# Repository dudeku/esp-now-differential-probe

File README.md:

# ESP-NOW Differential Probe Project

K. Dudek

### Framework: arduino-espressif32
>ver: 2.0.17
#### Lib Fixes:

```
in Ethernet.h
    class EthernetServer : public Server
    ->
    class EthernetServer : public Print
```

OR
```
in Ethernet.h in line 261:
	virtual void begin();
    ->
	virtual void begin(uint16_t port=0);

and in EthernetServer.cpp in line 28:
    void EthernetServer::begin()
    ->
    void EthernetServer::begin(uint16_t port_not_used)
```

#### Problems in framework version 3.x:
```
spi3 problem, not setting pinMode MISO (6)
[ ][E][esp32-hal-gpio.c:190] __digitalRead(): IO 6 is not set as GPIO.
```
### tool-esptoolpy @ 4.8.1

## Possible fix for framework 3.x
```
digitalRead() in LTC2449 lib cannot access MISO pin to check if transmission has been completed.

need to change LIC2449 library implementation for new version.
```

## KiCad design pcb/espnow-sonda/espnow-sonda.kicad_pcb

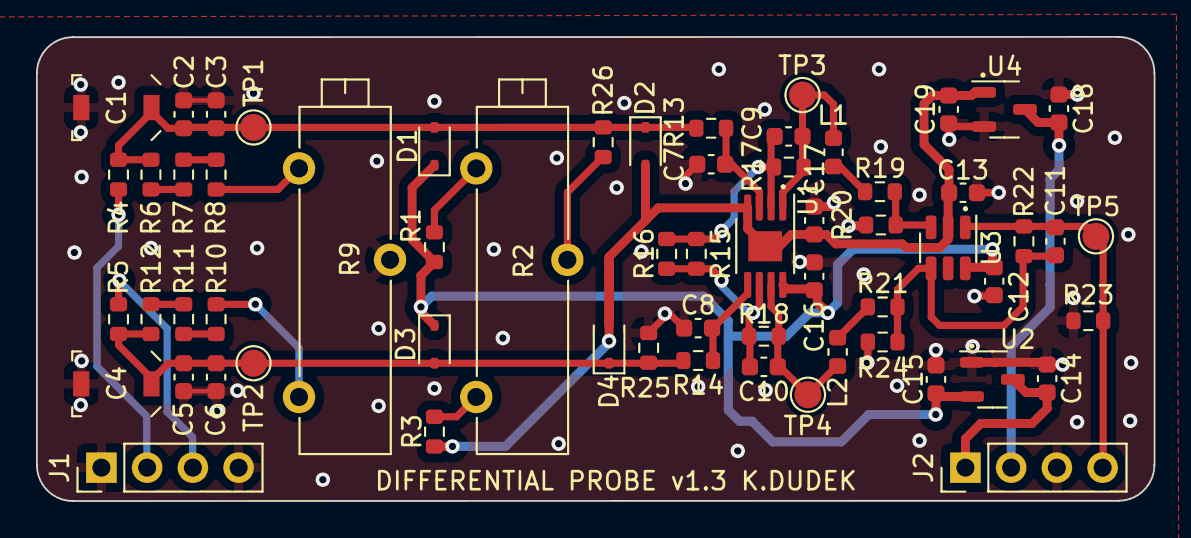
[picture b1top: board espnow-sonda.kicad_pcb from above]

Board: 2 copper layers, 62.1 x 25.8 mm, 62 parts (0 on the bottom side), 29 nets.

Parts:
C1, C4: C_Trimmer_Voltronics_JZ
C2, C3, C5, C6: C_0603_1608Metric
C7, C8, C9, C10, C11: 10p; C_0603_1608Metric
C12, C13, C16, C17: 0.1µ; C_0603_1608Metric
C14, C15, C18, C19: 1µ; C_0603_1608Metric
D1, D2, D3, D4: BAS316,115; D_SOD-323
J1, J2: PinHeader_1x04_P2.54mm_Vertical
L1, L2: r0; L_0603_1608Metric
R1, R3: 1M; R_0603_1608Metric
R2: 1M; Potentiometer_Bourns_3006W_Horizontal
R4, R5, R13, R14: 150; R_0603_1608Metric
R6, R12: 9.1k; R_0603_1608Metric
R7, R11: 845; R_0603_1608Metric
R8, R10: 24.9; R_0603_1608Metric
R9: 100; Potentiometer_Bourns_3006W_Horizontal
R15: 16; R_0603_1608Metric
R16, R24: R_0603_1608Metric
R17, R18: 470; R_0603_1608Metric
R19, R20, R21, R22: 348; R_0603_1608Metric
R23: 1k; R_0603_1608Metric
R25, R26: 750k; R_0603_1608Metric
TP1, TP2, TP4, TP5: TestPoint_Pad_D1.5mm
TP3: Test Point; TestPoint_Pad_D1.5mm
U1: LTC6269; MSOP-8-1EP_3x3mm_P0.65mm_EP1.68x1.88mm
U2: XC6206P251; SOT-23-3
U3: LMH6611; SOT-23-6
U4: XC6902N251; SOT-23-3

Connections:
4V8: C12.2, C15.2, C16.2, D1.1, D3.1, R1.1, U1.8 (V+), U2.2 (VO), U3.6 (V+)
-4V8: C13.2, C17.2, C19.2, D2.2, D4.2, R3.2, U1.4 (V-), U1.9 (V-), U3.2 (V-), U4.1 (VO)
/IN_N: J1.3, R5.1
/IN_P: J1.2, R4.1
/VCC5V: C14.2, J2.1, U2.3 (VI)
/VEE-5V: C18.2, J2.2, U4.3 (VI)
/VOUT: C11.2, J2.4, R22.2, R23.2, TP5.1 (TP), U3.1
GND: C1.2, C2.1, C3.1, C4.2, C5.1, C6.1, C7.1, C8.1, C12.1, C13.1, C14.1, C15.1, C16.1, C17.1, C18.1, C19.1, J1.1, J1.4, J2.3, R9.2, R20.2, R23.1, R24.1, R25.1, U2.1 (GND), U4.2 (GND)
unnamed: L1.2, R19.1
unnamed: L2.2, R21.1
unnamed: R1.2, R2.3
unnamed: R2.1, R3.1
unnamed: R2.2, R26.1
unnamed: R6.1, R7.2
unnamed: R7.1, R8.2
unnamed: R8.1, R9.3
unnamed: R9.1, R10.1
unnamed: R10.2, R11.1
unnamed: R11.2, R12.1
unnamed: C1.1, C2.2, C3.2, D1.2, D2.1, R4.2, R6.2, R13.1, R26.2, TP1.1 (TP)
unnamed: C4.1, C5.2, C6.2, D3.2, D4.1, R5.2, R12.2, R14.1, R25.2, TP2.1 (TP)
unnamed: C9.2, L1.1, R17.2, TP3.1 (TP), U1.1
unnamed: C10.2, L2.1, R18.2, TP4.1 (TP), U1.7
unnamed: C7.2, R13.2, U1.3 (+)
unnamed: C9.1, R15.1, R16.1, R17.1, U1.2 (-)
unnamed: C8.2, R14.2, U1.5 (+)
unnamed: C10.1, R15.2, R16.2, R18.1, U1.6 (-)
unnamed: R19.2, R20.1, U3.3 (+)
unnamed: C11.1, R21.2, R22.1, R24.2, U3.4 (-)

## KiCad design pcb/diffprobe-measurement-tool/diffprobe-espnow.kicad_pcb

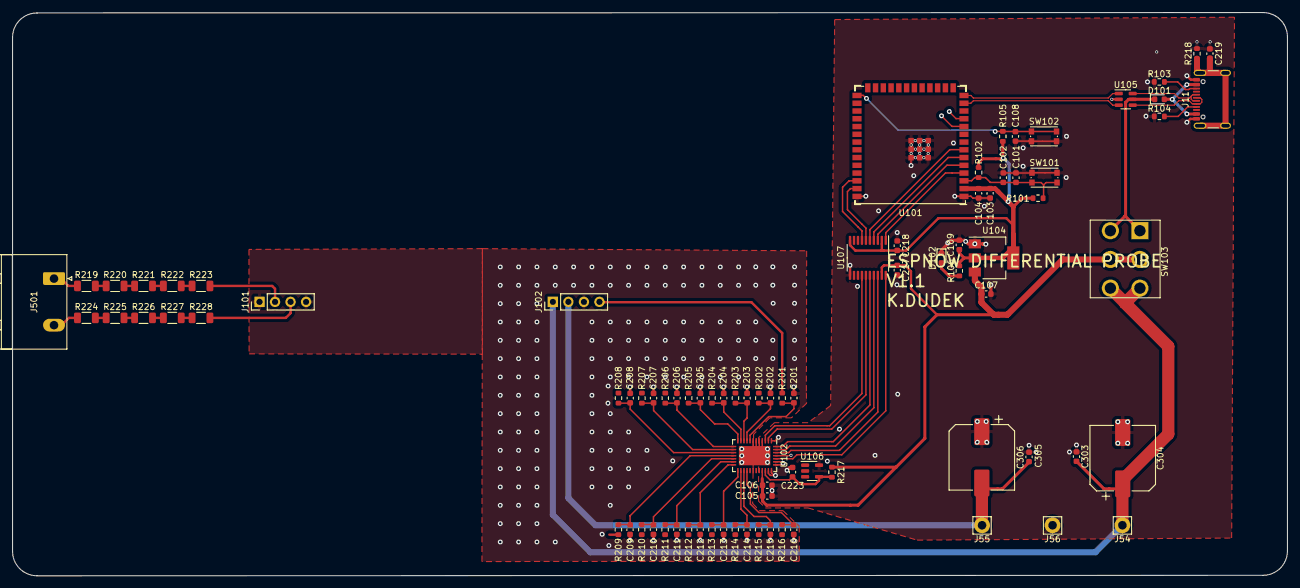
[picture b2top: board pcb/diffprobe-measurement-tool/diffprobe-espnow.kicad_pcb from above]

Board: 2 copper layers, 208.6 x 92.2 mm, 85 parts (0 on the bottom side), 59 nets.

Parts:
C101, C103, C108: 100n; C_0603_1608Metric
C102, C107, C303, C305: 1u; C_0603_1608Metric
C104, C106: 10u; C_0603_1608Metric
C105, C217, C218: 0.1u; C_0603_1608Metric
C109: 4.7u; C_0603_1608Metric
C201, C202, C203, C204, C205, C206, C207, C208, C209, C210, C211, C212, C213, C214, C215, C216, C223: 470pF; C_0603_1608Metric
C219: 4n7F; C_0603_1608Metric
C304, C306: 100u; CP_Elec_10x12.5
D101: NSR20F30NXT5G; D_0603_1608Metric
D102: LED; LED_0603_1608Metric
J11: USB_C_Receptacle_USB2.0; USB_C_Receptacle_GCT_USB4105-xx-A_16P_TopMnt_Horizontal
J54: 5V; Pin_D1.4mm_L8.5mm_W2.8mm_FlatFork
J55: -5V; Pin_D1.4mm_L8.5mm_W2.8mm_FlatFork
J56: GND; Pin_D1.4mm_L8.5mm_W2.8mm_FlatFork
J101, J102: Conn_01x04_Socket; PinHeader_1x04_P2.54mm_Vertical
J501: Screw_Terminal_01x02; PhoenixContact_GMSTBA_2,5_2-G-7,62_1x02_P7.62mm_Horizontal
R101, R102, R105: 10k; R_0603_1608Metric
R103, R104: 5.1k; R_0603_1608Metric
R106, R217: 1k; R_0603_1608Metric
R201: 100k; R_0603_1608Metric
R202, R203, R204, R205, R206, R207, R208, R209, R210, R211, R212, R213, R214, R215, R216: 470R; R_0603_1608Metric
R218: 1MEG; R_0603_1608Metric
R219, R220, R221, R222, R223, R224, R225, R226, R227, R228: 1MEG; R_1206_3216Metric
SW101, SW102: SW_Push; SW_Push_1P1T_NO_CK_KMR2
SW103: 500SDP1S1M2QEA; SW_PUSH_E-Switch_500SDP1S1M2QEA
U101: ESP32-S3-WROOM-1; ESP32-S3-WROOM-1U
U102: LTC2448CUHF-PBF; QFN-38-1EP_5x7mm_P0.5mm_EP3.15x5.15mm
U104: LDL1117S33R; SOT-223-3_TabPin2
U105: USBLC6-2SC6; SOT-23-6
U106: LM4030-2.5; SOT-23-5
U107: TXB0108PW; TSSOP-20_4.4x6.5mm_P0.65mm

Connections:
/PS5V: C303.1, C304.1, J54.1, J102.1, SW103.3 (C), SW103.6 (C)
/PS-5V: C305.1, C306.2, J55.1, J102.2
/esp32andadc/CH0: J102.4, R201.2
/esp32andadc/D+: U101.14 (GPIO20/U1CTS/ADC2_CH9/CLK_OUT1/USB_D+), U105.1 (I/O1)
/esp32andadc/D-: U101.13 (GPIO19/U1RTS/ADC2_CH8/CLK_OUT2/USB_D-), U105.3 (I/O2)
/esp32andadc/Din+: J11.A6 (D+), J11.B6 (D+), U105.6 (I/O1)
/esp32andadc/Din-: J11.A7 (D-), J11.B7 (D-), U105.4 (I/O2)
/esp32andadc/SHIELD: C219.2, J11.S1 (SHIELD), R218.1
/esp32andadc/USB5V: D101.1 (K), SW103.1 (A), SW103.4 (A), U105.5 (VBUS)
/esp32andadc/VCC3V3: C103.1, C104.1, C109.1, C218.2, R101.1, R102.1, R105.1, R106.1, U101.2 (3V3), U104.2 (VO), U107.2 (VCCA), U107.10 (OE)
/esp32andadc/VCC5V: C105.1, C106.1, C107.1, C217.1, R217.1, SW103.2 (B), SW103.5 (B), U102.28 (VCC), U104.3 (VI), U107.19 (VCCB)
GND: C101.2, C102.2, C103.2, C104.2, C105.2, C106.2, C107.2, C108.2, C109.2, C201.2, C202.2, C203.2, C204.2, C205.2, C206.2, C207.2, C208.2, C209.2, C210.2, C211.2, C212.2, C213.2, C214.2, C215.2, C216.2, C217.2, C218.1, C219.1, C223.2, C303.2, C304.2, C305.2, C306.1, D102.1 (K), J11.A1 (GND), J11.A12 (GND), J11.B1 (GND), J11.B12 (GND), J56.1, J101.1, J101.4, J102.3, R103.2, R104.2, R218.2, SW101.1, SW102.2, U101.1 (GND), U101.40 (GND), U101.41 (GND), U102.1 (GND), U102.4 (GND), U102.5 (GND), U102.6 (GND), U102.7 (COM), U102.30 (REF-), U102.31 (GND), U102.32 (GND), U102.33 (GND), U102.35 (FO), U102.39 (EPAD), U104.1 (GND), U105.2 (GND), U106.5 (A), U107.11 (GND)
unnamed: D101.2 (A), J11.A4 (VBUS), J11.A9 (VBUS), J11.B4 (VBUS), J11.B9 (VBUS)
unnamed: D102.2 (A), R106.2
unnamed: J11.A5 (CC1), R104.1
unnamed: J11.B5 (CC2), R103.1
unnamed: J101.2, R223.2
unnamed: J101.3, R228.2
unnamed: J501.1, R219.1
unnamed: J501.2, R224.1
unnamed: R219.2, R220.1
unnamed: R220.2, R221.1
unnamed: R221.2, R222.1
unnamed: R222.2, R223.1
unnamed: R224.2, R225.1
unnamed: R225.2, R226.1
unnamed: R226.2, R227.1
unnamed: R227.2, R228.1
unnamed: C101.1, C102.1, R101.2, R102.2, SW101.2, U101.3 (EN)
unnamed: C108.1, R105.2, SW102.1, U101.27 (GPIO0/BOOT)
unnamed: U101.39 (GPIO1/TOUCH1/ADC1_CH0), U107.6 (A5)
unnamed: U101.38 (GPIO2/TOUCH2/ADC1_CH1), U107.7 (A6)
unnamed: U101.4 (GPIO4/TOUCH4/ADC1_CH3), U107.1 (A1)
unnamed: U101.5 (GPIO5/TOUCH5/ADC1_CH4), U107.3 (A2)
unnamed: U101.6 (GPIO6/TOUCH6/ADC1_CH5), U107.4 (A3)
unnamed: U101.7 (GPIO7/TOUCH7/ADC1_CH6), U107.5 (A4)
unnamed: U102.36 (*CS), U107.18 (B2)
unnamed: U102.3 (*EXT), U107.14 (B6)
unnamed: U102.2 (BUSY), U107.15 (B5)
unnamed: C201.1, R201.1, U102.8 (CH0)
unnamed: C202.1, R202.1, U102.9 (CH1)
unnamed: C203.1, R203.1, U102.10 (CH2)
unnamed: C204.1, R204.1, U102.11 (CH3)
unnamed: C205.1, R205.1, U102.12 (CH4)
unnamed: C206.1, R206.1, U102.13 (CH5)
unnamed: C207.1, R207.1, U102.14 (CH6)
unnamed: C208.1, R208.1, U102.15 (CH7)
unnamed: C209.1, R209.2, U102.16 (CH8)
unnamed: C210.1, R210.2, U102.17 (CH9)
unnamed: C211.1, R211.2, U102.18 (CH10)
unnamed: C212.1, R212.2, U102.19 (CH11)
unnamed: C213.1, R213.1, U102.20 (CH12)
unnamed: C214.1, R214.1, U102.21 (CH13)
unnamed: C215.1, R215.1, U102.22 (CH14)
unnamed: C216.1, R216.1, U102.23 (CH15)
unnamed: C223.1, R217.2, U102.29 (REF+), U106.4 (K)
unnamed: U102.38 (SCK), U107.16 (B4)
unnamed: U102.34 (SDI), U107.20 (B1)
unnamed: U102.37 (SDO), U107.17 (B3)

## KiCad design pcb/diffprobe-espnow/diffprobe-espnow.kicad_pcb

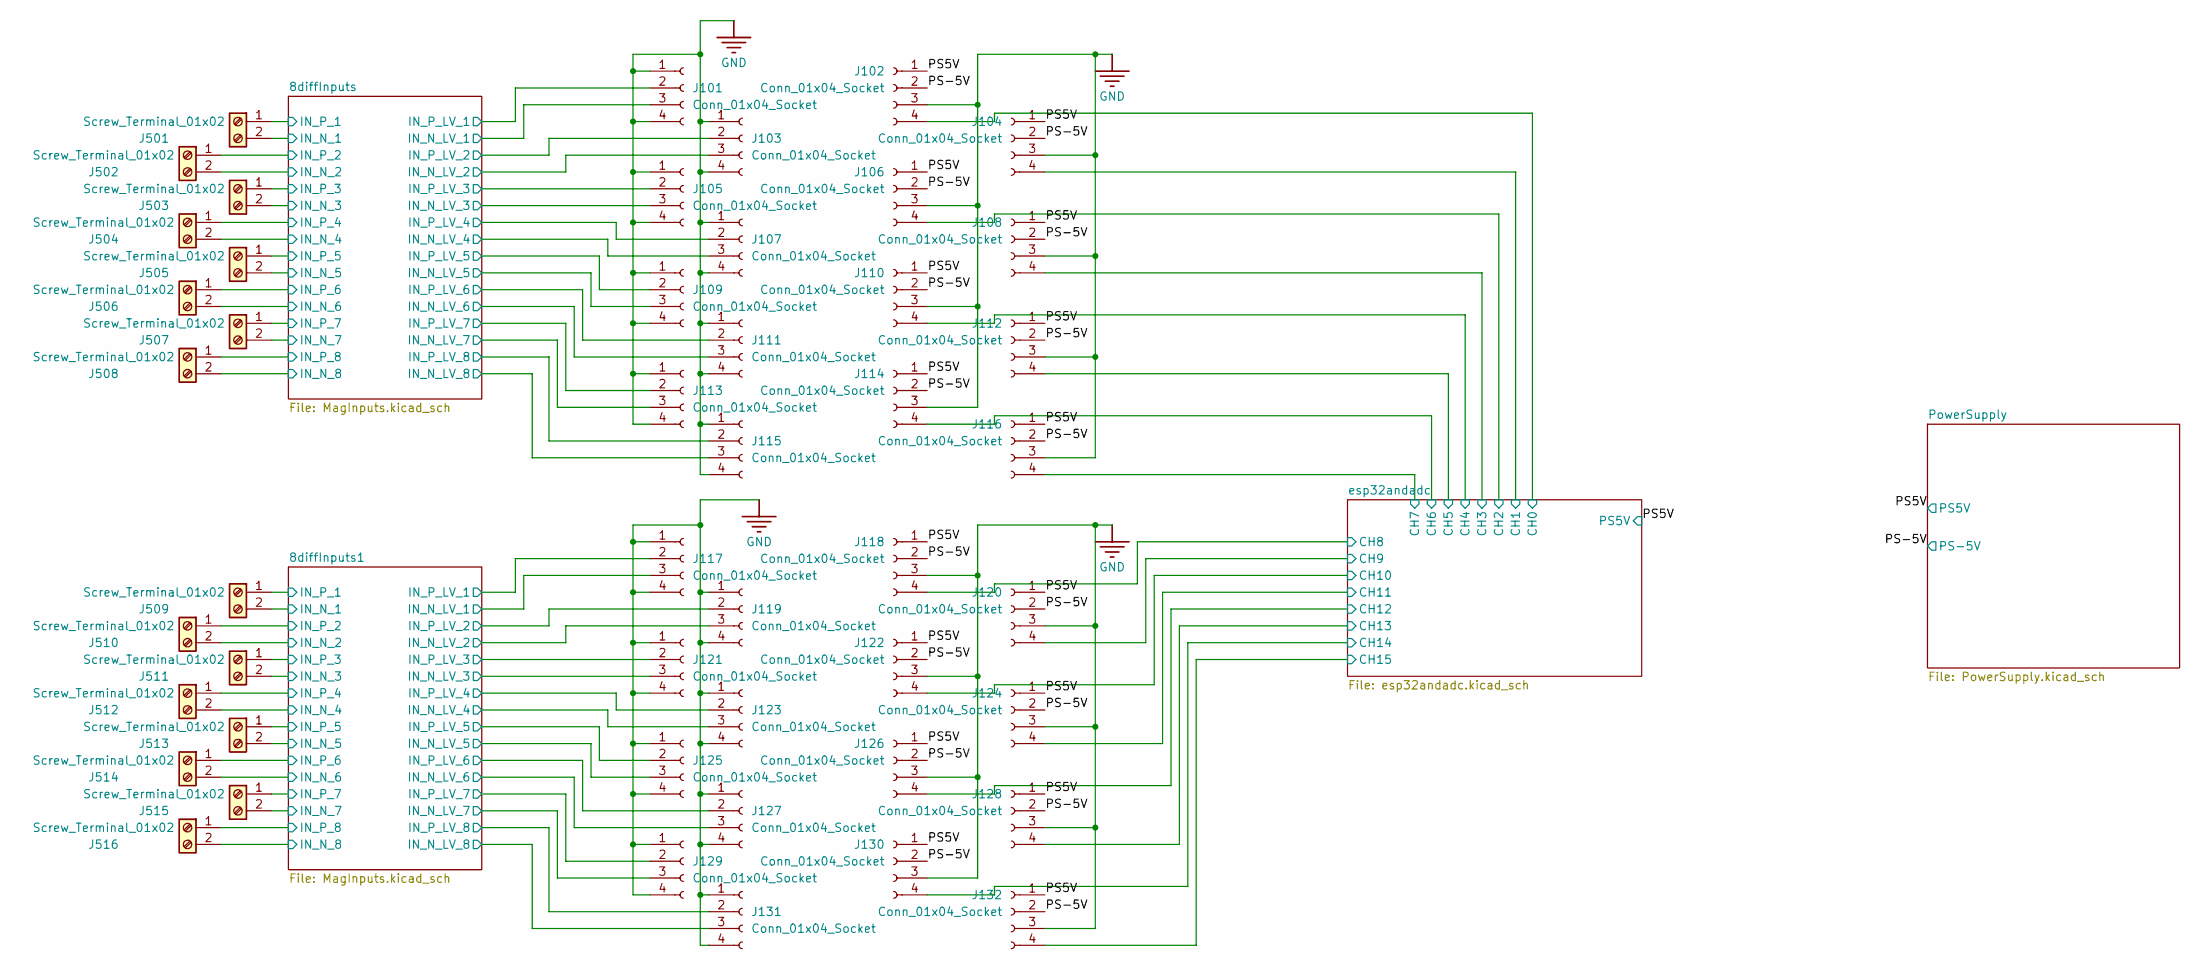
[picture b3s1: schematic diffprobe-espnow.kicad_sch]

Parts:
J101, J102, J103, J104, J105, J106, J107, J108, J109, J110, J111, J112, J113, J114, J115, J116, J117, J118, J119, J120, J121, J122, J123, J124, J125, J126, J127, J128, J129, J130, J131, J132: Conn_01x04_Socket; PinHeader_1x04_P2.54mm_Vertical
J501, J502, J503, J504, J505, J506, J507, J508, J509, J510, J511, J512, J513, J514, J515, J516: Screw_Terminal_01x02; PhoenixContact_GMSTBA_2,5_2-G-7,62_1x02_P7.62mm_Horizontal

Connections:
/8diffInputs1/IN_N_1: J509.2; also elsewhere on the board
/8diffInputs1/IN_N_2: J510.2; also elsewhere on the board
/8diffInputs1/IN_N_3: J511.2; also elsewhere on the board
/8diffInputs1/IN_N_4: J512.2; also elsewhere on the board
/8diffInputs1/IN_N_5: J513.2; also elsewhere on the board
/8diffInputs1/IN_N_6: J514.2; also elsewhere on the board
/8diffInputs1/IN_N_7: J515.2; also elsewhere on the board
/8diffInputs1/IN_N_8: J516.2; also elsewhere on the board
/8diffInputs1/IN_N_LV_1: J117.3; also elsewhere on the board
/8diffInputs1/IN_N_LV_2: J119.3; also elsewhere on the board
/8diffInputs1/IN_N_LV_3: J121.3; also elsewhere on the board
/8diffInputs1/IN_N_LV_4: J123.3; also elsewhere on the board
/8diffInputs1/IN_N_LV_5: J125.3; also elsewhere on the board
/8diffInputs1/IN_N_LV_6: J127.3; also elsewhere on the board
/8diffInputs1/IN_N_LV_7: J129.3; also elsewhere on the board
/8diffInputs1/IN_N_LV_8: J131.3; also elsewhere on the board
/8diffInputs1/IN_P_1: J509.1; also elsewhere on the board
/8diffInputs1/IN_P_2: J510.1; also elsewhere on the board
/8diffInputs1/IN_P_3: J511.1; also elsewhere on the board
/8diffInputs1/IN_P_4: J512.1; also elsewhere on the board
/8diffInputs1/IN_P_5: J513.1; also elsewhere on the board
/8diffInputs1/IN_P_6: J514.1; also elsewhere on the board
/8diffInputs1/IN_P_7: J515.1; also elsewhere on the board
/8diffInputs1/IN_P_8: J516.1; also elsewhere on the board
/8diffInputs1/IN_P_LV_1: J117.2; also elsewhere on the board
/8diffInputs1/IN_P_LV_2: J119.2; also elsewhere on the board
/8diffInputs1/IN_P_LV_3: J121.2; also elsewhere on the board
/8diffInputs1/IN_P_LV_4: J123.2; also elsewhere on the board
/8diffInputs1/IN_P_LV_5: J125.2; also elsewhere on the board
/8diffInputs1/IN_P_LV_6: J127.2; also elsewhere on the board
/8diffInputs1/IN_P_LV_7: J129.2; also elsewhere on the board
/8diffInputs1/IN_P_LV_8: J131.2; also elsewhere on the board
/8diffInputs/IN_N_1: J501.2; also elsewhere on the board
/8diffInputs/IN_N_2: J502.2; also elsewhere on the board
/8diffInputs/IN_N_3: J503.2; also elsewhere on the board
/8diffInputs/IN_N_4: J504.2; also elsewhere on the board
/8diffInputs/IN_N_5: J505.2; also elsewhere on the board
/8diffInputs/IN_N_6: J506.2; also elsewhere on the board
/8diffInputs/IN_N_7: J507.2; also elsewhere on the board
/8diffInputs/IN_N_8: J508.2; also elsewhere on the board
/8diffInputs/IN_N_LV_1: J101.3; also elsewhere on the board
/8diffInputs/IN_N_LV_2: J103.3; also elsewhere on the board
/8diffInputs/IN_N_LV_3: J105.3; also elsewhere on the board
/8diffInputs/IN_N_LV_4: J107.3; also elsewhere on the board
/8diffInputs/IN_N_LV_5: J109.3; also elsewhere on the board
/8diffInputs/IN_N_LV_6: J111.3; also elsewhere on the board
/8diffInputs/IN_N_LV_7: J113.3; also elsewhere on the board
/8diffInputs/IN_N_LV_8: J115.3; also elsewhere on the board
/8diffInputs/IN_P_1: J501.1; also elsewhere on the board
/8diffInputs/IN_P_2: J502.1; also elsewhere on the board
/8diffInputs/IN_P_3: J503.1; also elsewhere on the board
/8diffInputs/IN_P_4: J504.1; also elsewhere on the board
/8diffInputs/IN_P_5: J505.1; also elsewhere on the board
/8diffInputs/IN_P_6: J506.1; also elsewhere on the board
/8diffInputs/IN_P_7: J507.1; also elsewhere on the board
/8diffInputs/IN_P_8: J508.1; also elsewhere on the board
/8diffInputs/IN_P_LV_1: J101.2; also elsewhere on the board
/8diffInputs/IN_P_LV_2: J103.2; also elsewhere on the board
/8diffInputs/IN_P_LV_3: J105.2; also elsewhere on the board
/8diffInputs/IN_P_LV_4: J107.2; also elsewhere on the board
/8diffInputs/IN_P_LV_5: J109.2; also elsewhere on the board
/8diffInputs/IN_P_LV_6: J111.2; also elsewhere on the board
/8diffInputs/IN_P_LV_7: J113.2; also elsewhere on the board
/8diffInputs/IN_P_LV_8: J115.2; also elsewhere on the board
/PS5V: J102.1, J104.1, J106.1, J108.1, J110.1, J112.1, J114.1, J116.1, J118.1, J120.1, J122.1, J124.1, J126.1, J128.1, J130.1, J132.1; also elsewhere on the board
/PS-5V: J102.2, J104.2, J106.2, J108.2, J110.2, J112.2, J114.2, J116.2, J118.2, J120.2, J122.2, J124.2, J126.2, J128.2, J130.2, J132.2; also elsewhere on the board
/esp32andadc/CH0: J102.4; also elsewhere on the board
/esp32andadc/CH1: J104.4; also elsewhere on the board
/esp32andadc/CH2: J106.4; also elsewhere on the board
/esp32andadc/CH3: J108.4; also elsewhere on the board
/esp32andadc/CH4: J110.4; also elsewhere on the board
/esp32andadc/CH5: J112.4; also elsewhere on the board
/esp32andadc/CH6: J114.4; also elsewhere on the board
/esp32andadc/CH7: J116.4; also elsewhere on the board
/esp32andadc/CH8: J118.4; also elsewhere on the board
/esp32andadc/CH9: J120.4; also elsewhere on the board
/esp32andadc/CH10: J122.4; also elsewhere on the board
/esp32andadc/CH11: J124.4; also elsewhere on the board
/esp32andadc/CH12: J126.4; also elsewhere on the board
/esp32andadc/CH13: J128.4; also elsewhere on the board
/esp32andadc/CH14: J130.4; also elsewhere on the board
/esp32andadc/CH15: J132.4; also elsewhere on the board
GND: J101.1, J101.4, J102.3, J103.1, J103.4, J104.3, J105.1, J105.4, J106.3, J107.1, J107.4, J108.3, J109.1, J109.4, J110.3, J111.1, J111.4, J112.3, J113.1, J113.4, J114.3, J115.1, J115.4, J116.3, J117.1, J117.4, J118.3, J119.1, J119.4, J120.3, J121.1, J121.4, J122.3, J123.1, J123.4, J124.3, J125.1, J125.4, J126.3, J127.1, J127.4, J128.3, J129.1, J129.4, J130.3, J131.1, J131.4, J132.3; also elsewhere on the board

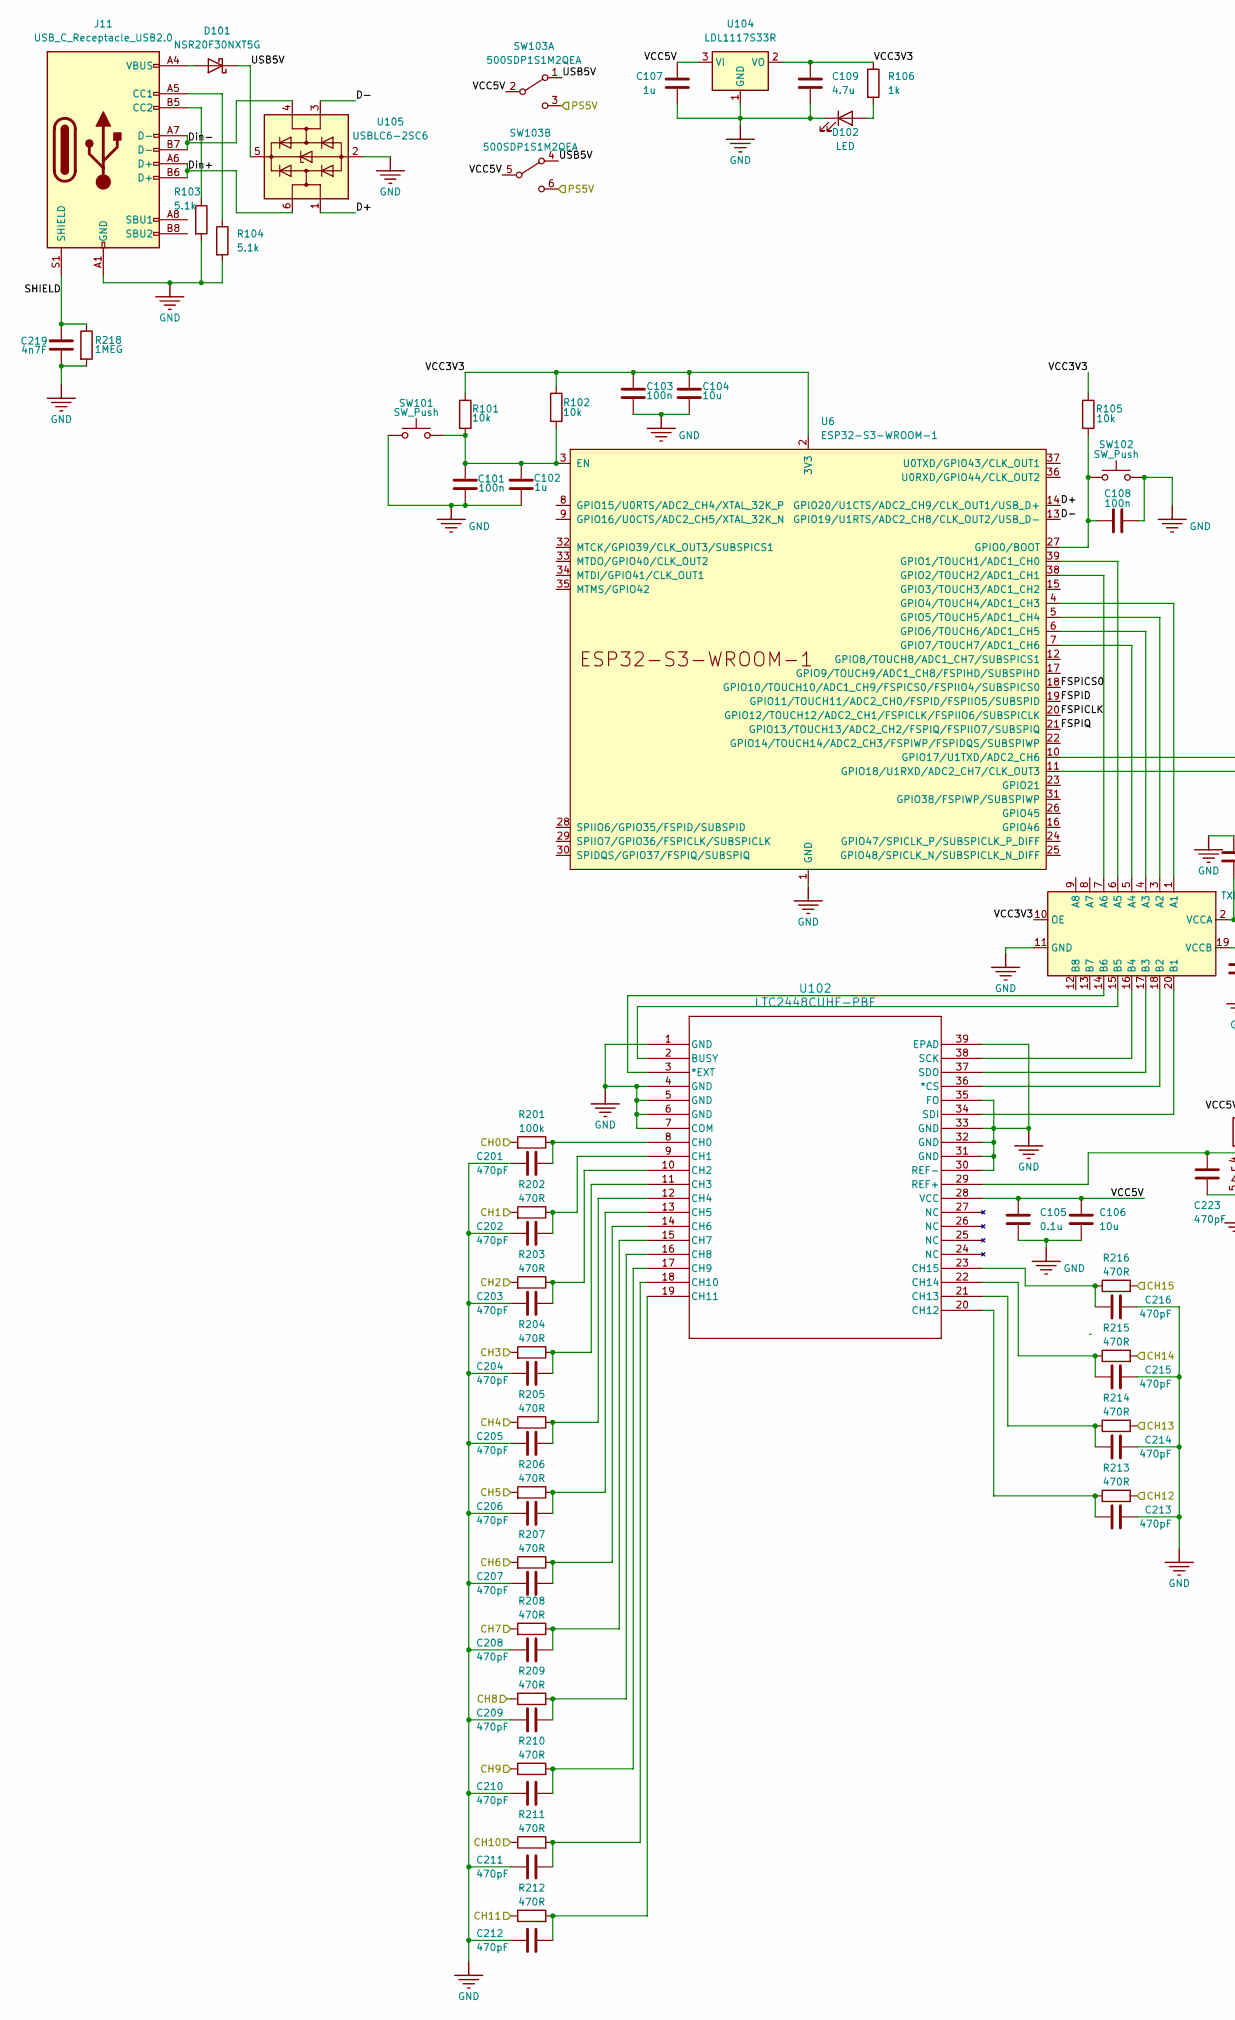
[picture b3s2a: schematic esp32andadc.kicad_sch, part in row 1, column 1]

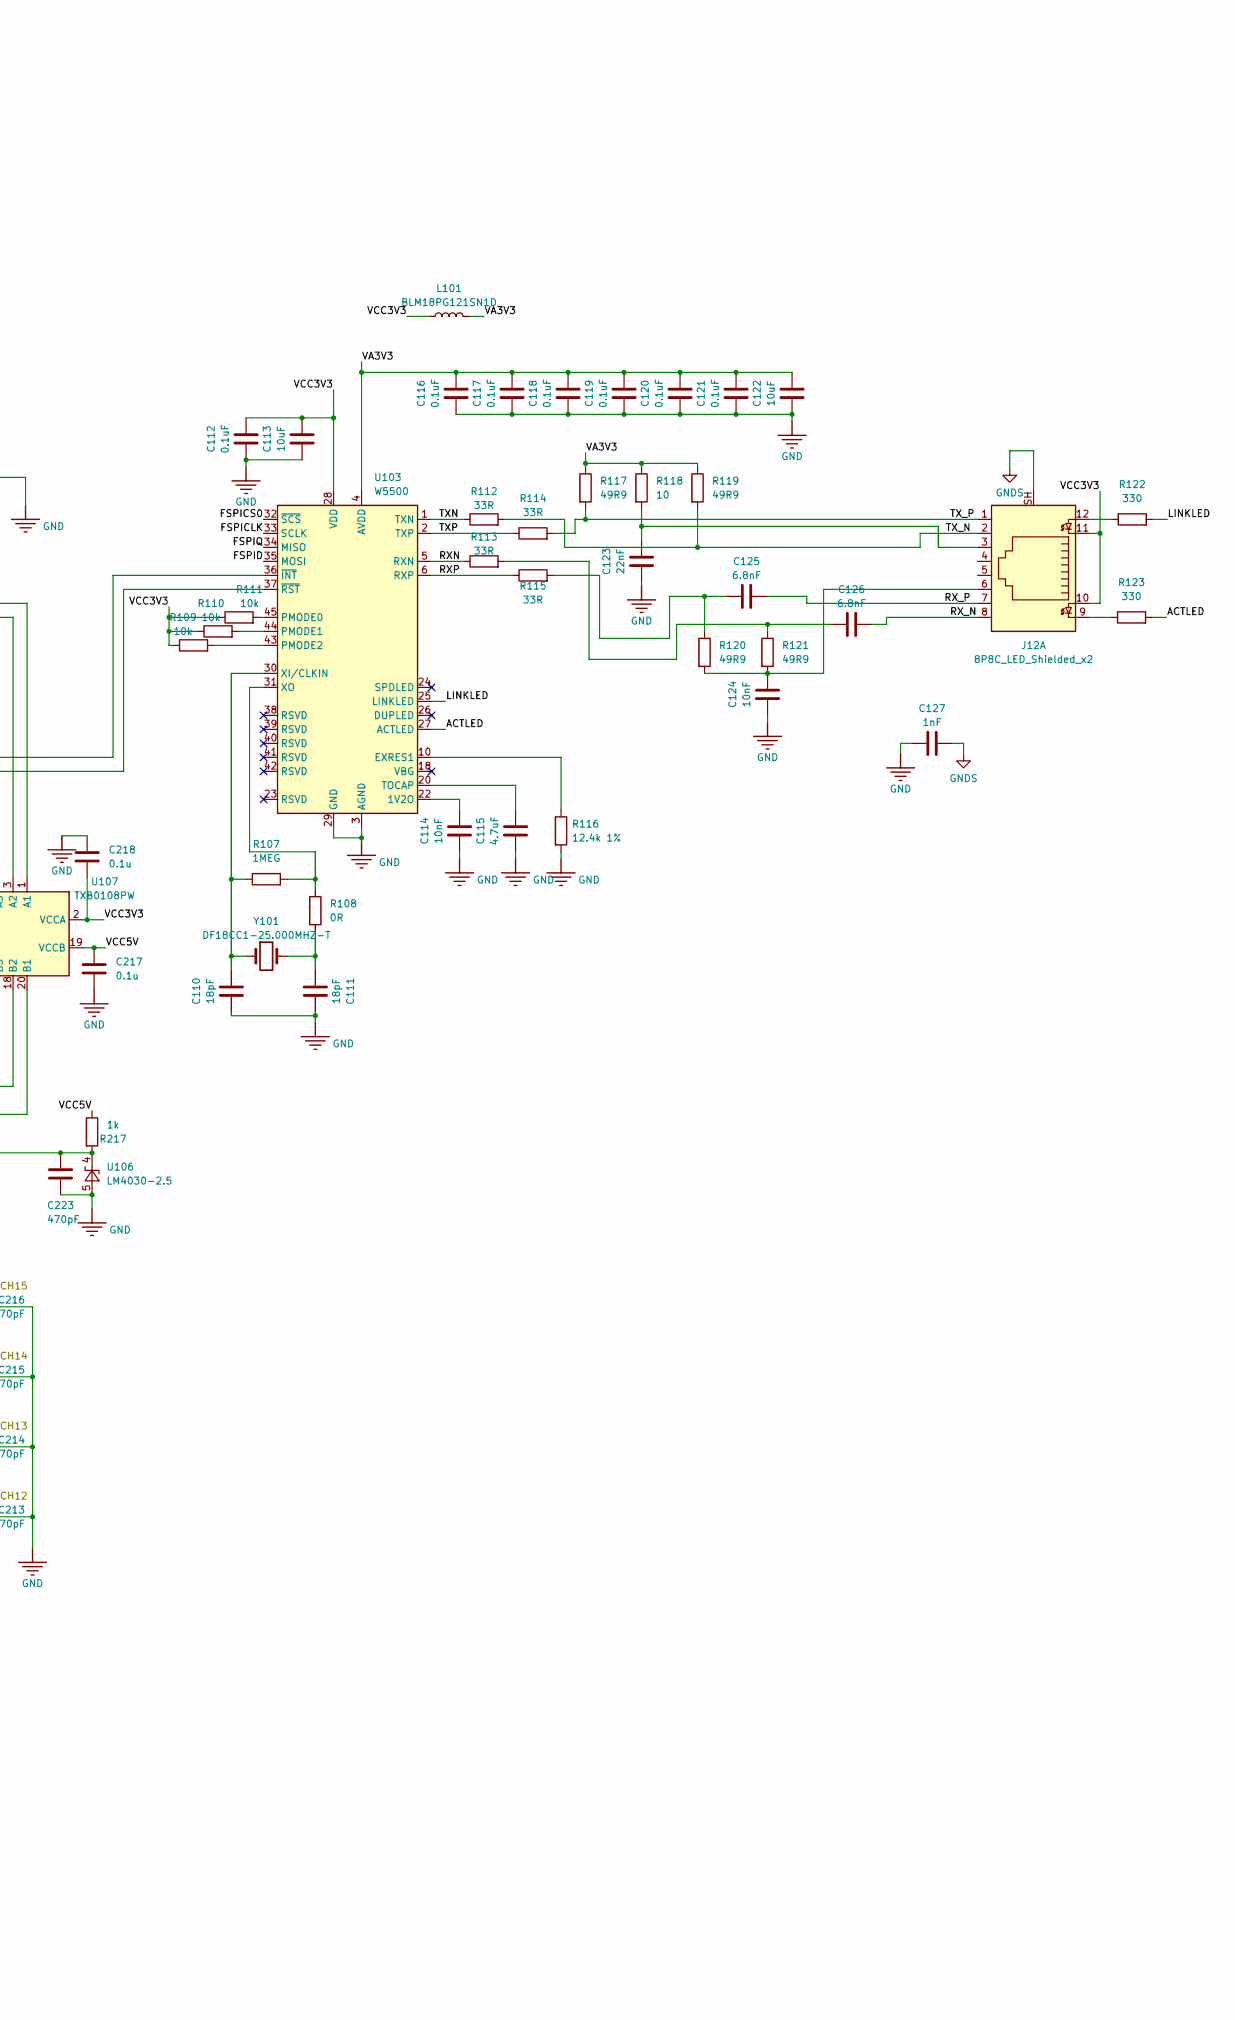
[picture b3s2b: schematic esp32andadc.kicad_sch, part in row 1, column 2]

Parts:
C101, C103, C108: 100n; C_0603_1608Metric
C102, C107: 1u; C_0603_1608Metric
C104, C106: 10u; C_0603_1608Metric
C105, C217, C218: 0.1u; C_0603_1608Metric
C109: 4.7u; C_0603_1608Metric
C110, C111: 18pF; C_0603_1608Metric
C112, C116, C117, C118, C119, C120, C121: 0.1uF; C_0603_1608Metric
C113, C122: 10uF; C_0603_1608Metric
C114, C124: 10nF; C_0603_1608Metric
C115: 4.7uF; C_0603_1608Metric
C123: 22nF; C_0603_1608Metric
C125, C126: 6.8nF; C_0603_1608Metric
C127: 1nF; C_0603_1608Metric
C201, C202, C203, C204, C205, C206, C207, C208, C209, C210, C211, C212, C213, C214, C215, C216, C223: 470pF; C_0603_1608Metric
C219: 4n7F; C_0603_1608Metric
D101: NSR20F30NXT5G; D_0603_1608Metric
D102: LED; LED_0603_1608Metric
J11: USB_C_Receptacle_USB2.0; USB_C_Receptacle_GCT_USB4105-xx-A_16P_TopMnt_Horizontal
J12: 8P8C_LED_Shielded_x2; CONN12_5-2301994-8_TEC
L101: BLM18PG121SN1D; L_0603_1608Metric
R101, R102, R105, R109, R110, R111: 10k; R_0603_1608Metric
R103, R104: 5.1k; R_0603_1608Metric
R106, R217: 1k; R_0603_1608Metric
R107, R218: 1MEG; R_0603_1608Metric
R108: 0R; R_0603_1608Metric
R112, R113, R114, R115: 33R; R_0603_1608Metric
R116: 12.4k 1%; R_0603_1608Metric
R117, R119, R120, R121: 49R9; R_0603_1608Metric
R118: 10; R_0603_1608Metric
R122, R123: 330; R_0603_1608Metric
R201: 100k; R_0603_1608Metric
R202, R203, R204, R205, R206, R207, R208, R209, R210, R211, R212, R213, R214, R215, R216: 470R; R_0603_1608Metric
SW101, SW102: SW_Push; SW_Push_1P1T_NO_CK_KMR2
SW103: 500SDP1S1M2QEA; SW_PUSH_E-Switch_500SDP1S1M2QEA
U6: ESP32-S3-WROOM-1; ESP32-S3-WROOM-1U
U102: LTC2448CUHF-PBF; QFN-38-1EP_5x7mm_P0.5mm_EP3.15x5.15mm
U103: W5500; LQFP-48_7x7mm_P0.5mm
U104: LDL1117S33R; SOT-223-3_TabPin2
U105: USBLC6-2SC6; SOT-23-6
U106: LM4030-2.5; SOT-23-5
U107: TXB0108PW; TSSOP-20_4.4x6.5mm_P0.65mm
Y101: DF18CC1-25.000MHZ-T; Crystal_SMD_HC49-SD

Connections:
/PS5V: SW103.3 (C), SW103.6 (C); also elsewhere on the board
/esp32andadc/ACTLED: R123.2, U103.27 (ACTLED)
/esp32andadc/CH0: R201.2; also elsewhere on the board
/esp32andadc/CH1: R202.2; also elsewhere on the board
/esp32andadc/CH2: R203.2; also elsewhere on the board
/esp32andadc/CH3: R204.2; also elsewhere on the board
/esp32andadc/CH4: R205.2; also elsewhere on the board
/esp32andadc/CH5: R206.2; also elsewhere on the board
/esp32andadc/CH6: R207.2; also elsewhere on the board
/esp32andadc/CH7: R208.2; also elsewhere on the board
/esp32andadc/CH8: R209.1; also elsewhere on the board
/esp32andadc/CH9: R210.1; also elsewhere on the board
/esp32andadc/CH10: R211.1; also elsewhere on the board
/esp32andadc/CH11: R212.1; also elsewhere on the board
/esp32andadc/CH12: R213.2; also elsewhere on the board
/esp32andadc/CH13: R214.2; also elsewhere on the board
/esp32andadc/CH14: R215.2; also elsewhere on the board
/esp32andadc/CH15: R216.2; also elsewhere on the board
/esp32andadc/D+: U105.1 (I/O1); also elsewhere on the board
/esp32andadc/D-: U105.3 (I/O2); also elsewhere on the board
/esp32andadc/Din+: J11.A6 (D+), J11.B6 (D+), U105.6 (I/O1)
/esp32andadc/Din-: J11.A7 (D-), J11.B7 (D-), U105.4 (I/O2)
/esp32andadc/FSPICLK: U103.33 (SCLK); also elsewhere on the board
/esp32andadc/FSPICS0: U103.32 (~SCS); also elsewhere on the board
/esp32andadc/FSPID: U103.35 (MOSI); also elsewhere on the board
/esp32andadc/FSPIQ: U103.34 (MISO); also elsewhere on the board
/esp32andadc/LINKLED: R122.2, U103.25 (LINKLED)
/esp32andadc/RXN: R113.1, U103.5 (RXN)
/esp32andadc/RXP: R115.1, U103.6 (RXP)
/esp32andadc/RX_N: C126.2, J12.8
/esp32andadc/RX_P: C125.2, J12.7
/esp32andadc/SHIELD: C219.2, J11.S1 (SHIELD), R218.1
/esp32andadc/TXN: R112.1, U103.1 (TXN)
/esp32andadc/TXP: R114.1, U103.2 (TXP)
/esp32andadc/TX_N: J12.2, R112.2, R119.2
/esp32andadc/TX_P: J12.1, R114.2, R117.2
/esp32andadc/USB5V: D101.1 (K), SW103.1 (A), SW103.4 (A), U105.5 (VBUS)
/esp32andadc/VA3V3: C116.2, C117.2, C118.2, C119.2, C120.2, C121.2, C122.2, L101.2, R117.1, R118.1, R119.1, U103.4 (AVDD), U103.8 (AVDD), U103.11 (AVDD), U103.15 (AVDD), U103.17 (AVDD), U103.21 (AVDD)
/esp32andadc/VCC3V3: C103.1, C104.1, C109.1, C112.2, C113.2, C218.2, J12.10, J12.11, L101.1, R101.1, R102.1, R105.1, R106.1, R109.1, R110.1, R111.1, U103.28 (VDD), U104.2 (VO), U107.2 (VCCA), U107.10 (OE); also elsewhere on the board
/esp32andadc/VCC5V: C105.1, C106.1, C107.1, C217.1, R217.1, SW103.2 (B), SW103.5 (B), U102.28 (VCC), U104.3 (VI), U107.19 (VCCB)
GND: C101.2, C102.2, C103.2, C104.2, C105.2, C106.2, C107.2, C108.2, C109.2, C110.1, C111.2, C112.1, C113.1, C114.1, C115.1, C116.1, C117.1, C118.1, C119.1, C120.1, C121.1, C122.1, C123.1, C124.1, C127.1, C201.2, C202.2, C203.2, C204.2, C205.2, C206.2, C207.2, C208.2, C209.2, C210.2, C211.2, C212.2, C213.2, C214.2, C215.2, C216.2, C217.2, C218.1, C219.1, C223.2, D102.1 (K), J11.A1 (GND), J11.A12 (GND), J11.B1 (GND), J11.B12 (GND), R103.2, R104.2, R116.2, R218.2, SW101.1, SW102.2, U102.1 (GND), U102.4 (GND), U102.5 (GND), U102.6 (GND), U102.7 (COM), U102.30 (REF-), U102.31 (GND), U102.32 (GND), U102.33 (GND), U102.35 (FO), U102.39 (EPAD), U103.3 (AGND), U103.9 (AGND), U103.14 (AGND), U103.16 (AGND), U103.19 (AGND), U103.29 (GND), U103.48 (AGND), U104.1 (GND), U105.2 (GND), U106.5 (A), U107.11 (GND); also elsewhere on the board
GNDS: C127.2, J12.SH
unnamed: C111.1, R108.2, Y101.2
unnamed: C123.2, J12.3, R118.2
unnamed: C124.2, J12.6, R120.2, R121.2
unnamed: C125.1, R115.2, R120.1
unnamed: C126.1, R113.2, R121.1
unnamed: D101.2 (A), J11.A4 (VBUS), J11.A9 (VBUS), J11.B4 (VBUS), J11.B9 (VBUS)
unnamed: D102.2 (A), R106.2
unnamed: J11.A5 (CC1), R104.1
unnamed: J11.B5 (CC2), R103.1
unnamed: J12.9, R123.1
unnamed: J12.12, R122.1
unnamed 252: C101.1, C102.1, R101.2, R102.2, SW101.2; also elsewhere on the board
unnamed 253: C108.1, R105.2, SW102.1; also elsewhere on the board
unnamed 254: U107.6 (A5); also elsewhere on the board
unnamed 255: U107.7 (A6); also elsewhere on the board
unnamed 256: U107.1 (A1); also elsewhere on the board
unnamed 257: U107.3 (A2); also elsewhere on the board
unnamed 258: U107.4 (A3); also elsewhere on the board
unnamed 259: U107.5 (A4); also elsewhere on the board
unnamed 260: U103.36 (~INT); also elsewhere on the board
unnamed 261: U103.37 (~RST); also elsewhere on the board
unnamed: U102.36 (*CS), U107.18 (B2)
unnamed: U102.3 (*EXT), U107.14 (B6)
unnamed: U102.2 (BUSY), U107.15 (B5)
unnamed: C201.1, R201.1, U102.8 (CH0)
unnamed: C202.1, R202.1, U102.9 (CH1)
unnamed: C203.1, R203.1, U102.10 (CH2)
unnamed: C204.1, R204.1, U102.11 (CH3)
unnamed: C205.1, R205.1, U102.12 (CH4)
unnamed: C206.1, R206.1, U102.13 (CH5)
unnamed: C207.1, R207.1, U102.14 (CH6)
unnamed: C208.1, R208.1, U102.15 (CH7)
unnamed: C209.1, R209.2, U102.16 (CH8)
unnamed: C210.1, R210.2, U102.17 (CH9)
unnamed: C211.1, R211.2, U102.18 (CH10)
unnamed: C212.1, R212.2, U102.19 (CH11)
unnamed: C213.1, R213.1, U102.20 (CH12)
unnamed: C214.1, R214.1, U102.21 (CH13)
unnamed: C215.1, R215.1, U102.22 (CH14)
unnamed: C216.1, R216.1, U102.23 (CH15)
unnamed: C223.1, R217.2, U102.29 (REF+), U106.4 (K)
unnamed: U102.38 (SCK), U107.16 (B4)
unnamed: U102.34 (SDI), U107.20 (B1)
unnamed: U102.37 (SDO), U107.17 (B3)
unnamed: C114.2, U103.22 (1V2O)
unnamed: R116.1, U103.10 (EXRES1)
unnamed: R111.2, U103.45 (PMODE0)
unnamed: R110.2, U103.44 (PMODE1)
unnamed: R109.2, U103.43 (PMODE2)
unnamed: C115.2, U103.20 (TOCAP)
unnamed: C110.2, R107.1, U103.30 (XI/CLKIN), Y101.1
unnamed: R107.2, R108.1, U103.31 (XO)

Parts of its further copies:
U101: ESP32-S3-WROOM-1; ESP32-S3-WROOM-1U

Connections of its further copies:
/esp32andadc/D+: U101.14 (GPIO20/U1CTS/ADC2_CH9/CLK_OUT1/USB_D+); also elsewhere on the board
/esp32andadc/D-: U101.13 (GPIO19/U1RTS/ADC2_CH8/CLK_OUT2/USB_D-); also elsewhere on the board
/esp32andadc/FSPICLK: U101.20 (GPIO12/TOUCH12/ADC2_CH1/FSPICLK/FSPIIO6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); also elsewhere on the board
/esp32andadc/FSPICS0: U101.18 (GPIO10/TOUCH10/ADC1_CH9/FSPICS0/FSPIIO4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); also elsewhere on the board
/esp32andadc/FSPID: U101.19 (GPIO11/TOUCH11/ADC2_CH0/FSPID/FSPIIO5/S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); also elsewhere on the board
/esp32andadc/FSPIQ: U101.21 (GPIO13/TOUCH13/ADC2_CH2/FSPIQ/FSPIIO7/S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); also elsewhere on the board
/esp32andadc/VCC3V3: U101.2 (3V3); also elsewhere on the board
GND: U101.1 (GND), U101.40 (GND), U101.41 (GND); also elsewhere on the board
unnamed 252: U101.3 (EN); also elsewhere on the board
unnamed 253: U101.27 (GPIO0/BOOT); also elsewhere on the board
unnamed 254: U101.39 (GPIO1/TOUCH1/ADC1_CH0); also elsewhere on the board
unnamed 255: U101.38 (GPIO2/TOUCH2/ADC1_CH1); also elsewhere on the board
unnamed 256: U101.4 (GPIO4/TOUCH4/ADC1_CH3); also elsewhere on the board
unnamed 257: U101.5 (GPIO5/TOUCH5/ADC1_CH4); also elsewhere on the board
unnamed 258: U101.6 (GPIO6/TOUCH6/ADC1_CH5); also elsewhere on the board
unnamed 259: U101.7 (GPIO7/TOUCH7/ADC1_CH6); also elsewhere on the board
unnamed 260: U101.10 (GPIO17/U1TXD/ADC2_CH6); also elsewhere on the board
unnamed 261: U101.11 (GPIO18/U1RXD/ADC2_CH7/CLK_OUT3); also elsewhere on the board
